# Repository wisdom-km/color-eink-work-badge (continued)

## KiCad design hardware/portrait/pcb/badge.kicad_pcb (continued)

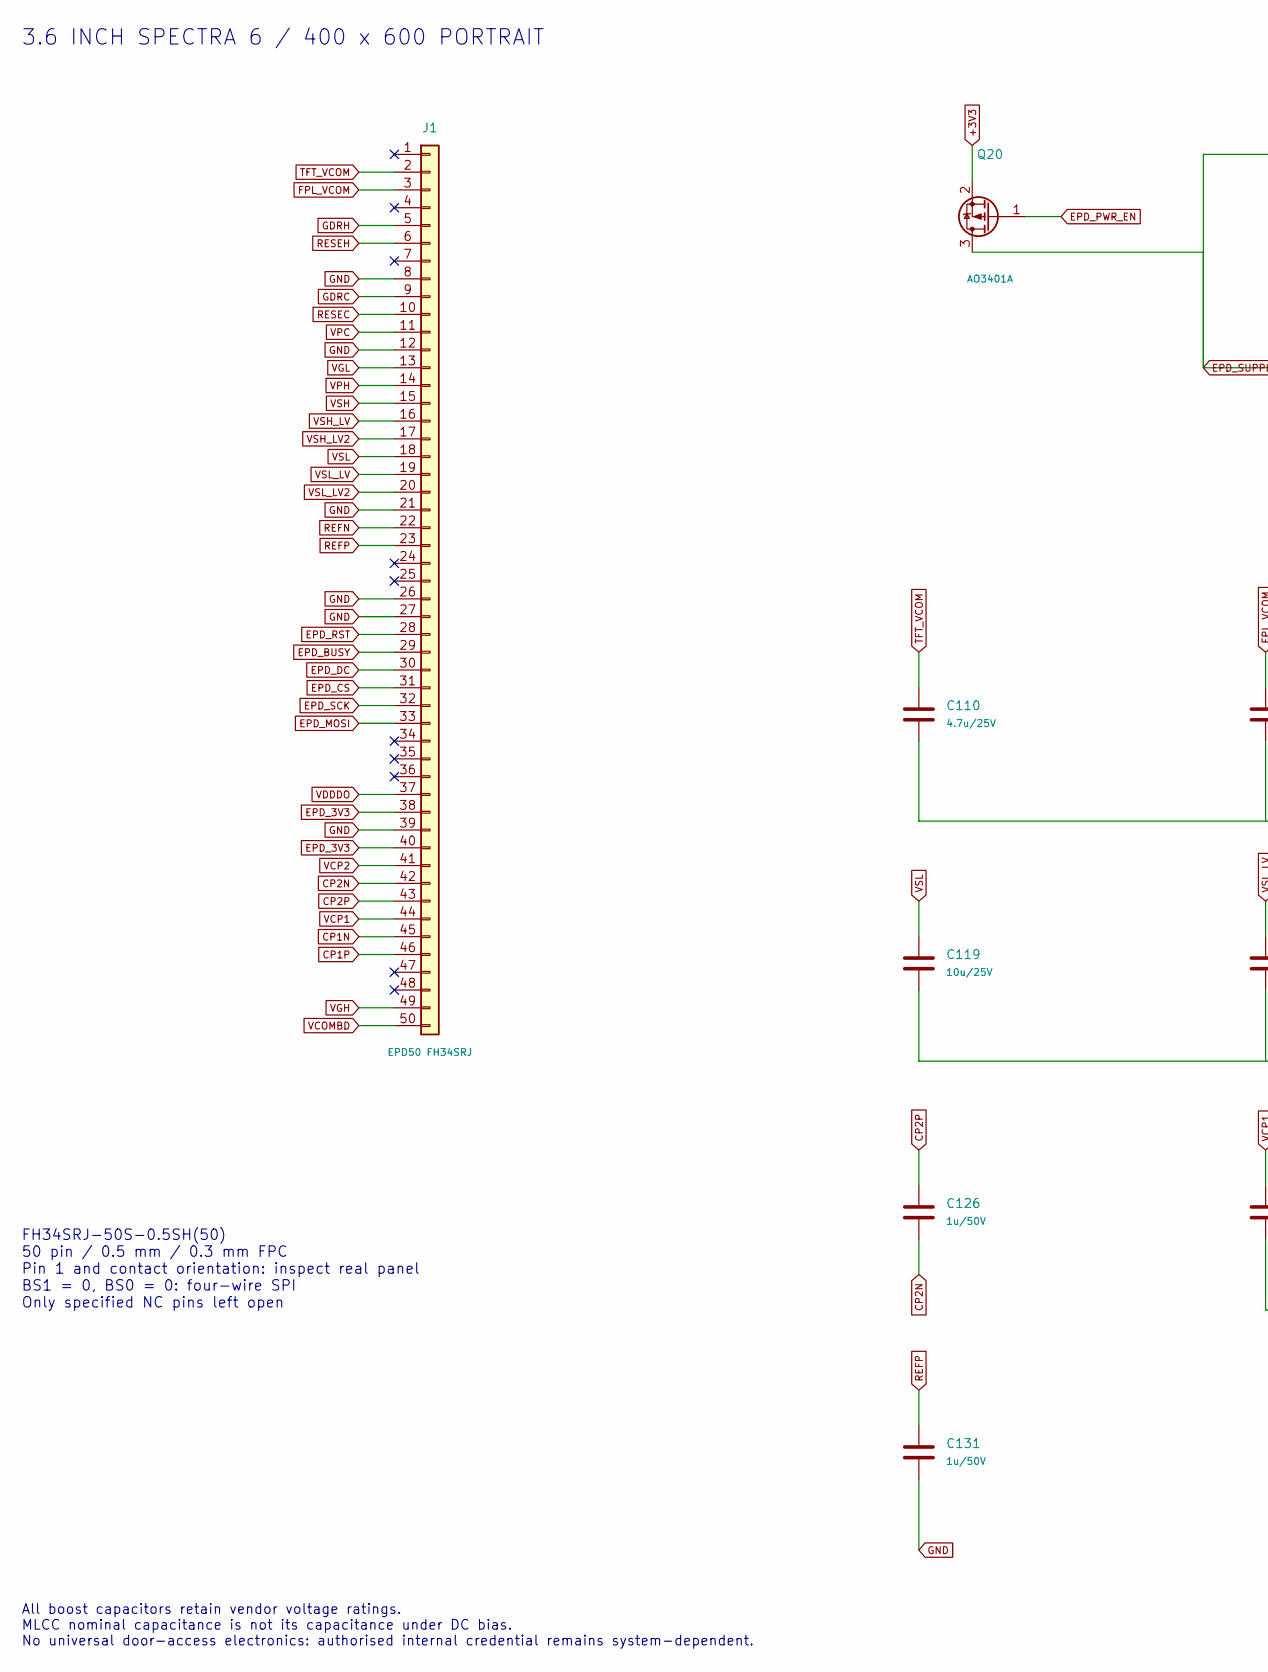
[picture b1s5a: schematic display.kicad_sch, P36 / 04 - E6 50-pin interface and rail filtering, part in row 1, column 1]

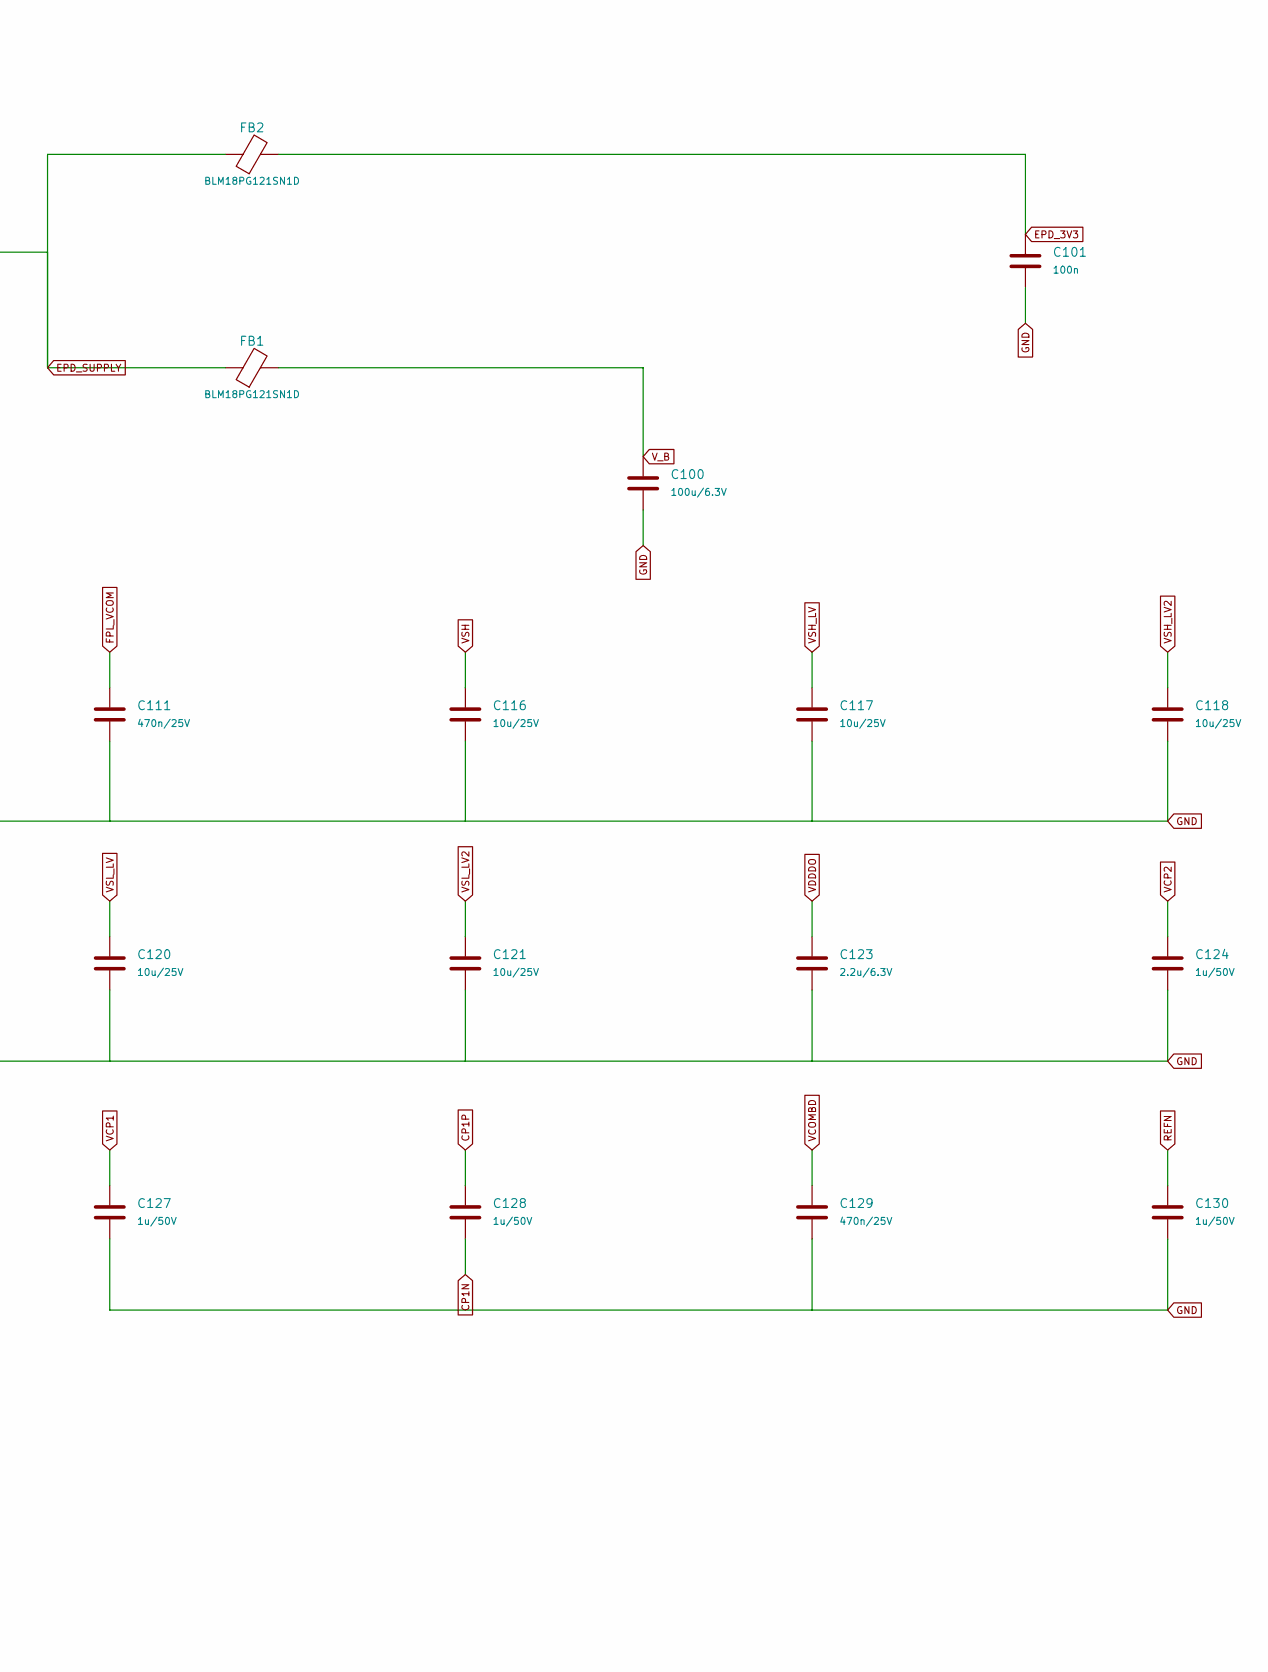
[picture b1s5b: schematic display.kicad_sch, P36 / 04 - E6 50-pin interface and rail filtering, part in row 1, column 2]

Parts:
C100: 100u/6.3V; C_1210_3225Metric
C101: 100n; C_0402_1005Metric
C110: 4.7u/25V; C_0805_2012Metric
C111, C129: 470n/25V; C_0805_2012Metric
C116, C117, C118, C119, C120, C121: 10u/25V; C_0805_2012Metric
C123: 2.2u/6.3V; C_0805_2012Metric
C124, C126, C127, C128, C130, C131: 1u/50V; C_0805_2012Metric
FB1, FB2: BLM18PG121SN1D; L_0603_1608Metric
J1: EPD50 FH34SRJ; FH34SRJ-50S-0.5SH
Q20: AO3401A; SOT-23

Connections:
+3V3: Q20.2 (S); also elsewhere on the board
CP1N: C128.2, J1.45
CP1P: C128.1, J1.46
CP2N: C126.2, J1.42
CP2P: C126.1, J1.43
EPD_3V3: C101.1, FB2.2, J1.38, J1.40
EPD_BUSY: J1.29; also elsewhere on the board
EPD_CS: J1.31; also elsewhere on the board
EPD_DC: J1.30; also elsewhere on the board
EPD_MOSI: J1.33; also elsewhere on the board
EPD_PWR_EN: Q20.1 (G); also elsewhere on the board
EPD_RST: J1.28; also elsewhere on the board
EPD_SCK: J1.32; also elsewhere on the board
EPD_SUPPLY: FB1.1, FB2.1, Q20.3 (D)
FPL_VCOM: C111.1, J1.3
GDRC: J1.9; also elsewhere on the board
GDRH: J1.5; also elsewhere on the board
GND: C100.2, C101.2, C110.2, C111.2, C116.2, C117.2, C118.2, C119.2, C120.2, C121.2, C123.2, C124.2, C127.2, C129.2, C130.2, C131.2, J1.8, J1.12, J1.21, J1.26, J1.27, J1.39; also elsewhere on the board
REFN: C130.1, J1.22
REFP: C131.1, J1.23
RESEC: J1.10; also elsewhere on the board
RESEH: J1.6; also elsewhere on the board
TFT_VCOM: C110.1, J1.2
VCOMBD: C129.1, J1.50
VCP1: C127.1, J1.44
VCP2: C124.1, J1.41
VDDDO: C123.1, J1.37
VGH: J1.49; also elsewhere on the board
VGL: J1.13; also elsewhere on the board
VPC: J1.11; also elsewhere on the board
VPH: J1.14; also elsewhere on the board
VSH: C116.1, J1.15
VSH_LV: C117.1, J1.16
VSH_LV2: C118.1, J1.17
VSL: C119.1, J1.18
VSL_LV: C120.1, J1.19
VSL_LV2: C121.1, J1.20
V_B: C100.1, FB1.2; also elsewhere on the board

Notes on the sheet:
3.6 INCH SPECTRA 6 / 400 x 600 PORTRAIT
FH34SRJ-50S-0.5SH(50) 50 pin / 0.5 mm / 0.3 mm FPC Pin 1 and contact orientation: inspect real panel BS1 = 0, BS0 = 0: four-wire SPI Only specified NC pins left open
All boost capacitors retain vendor voltage ratings. MLCC nominal capacitance is not its capacitance under DC bias. No universal door-access electronics: authorised internal credential remains system-dependent.

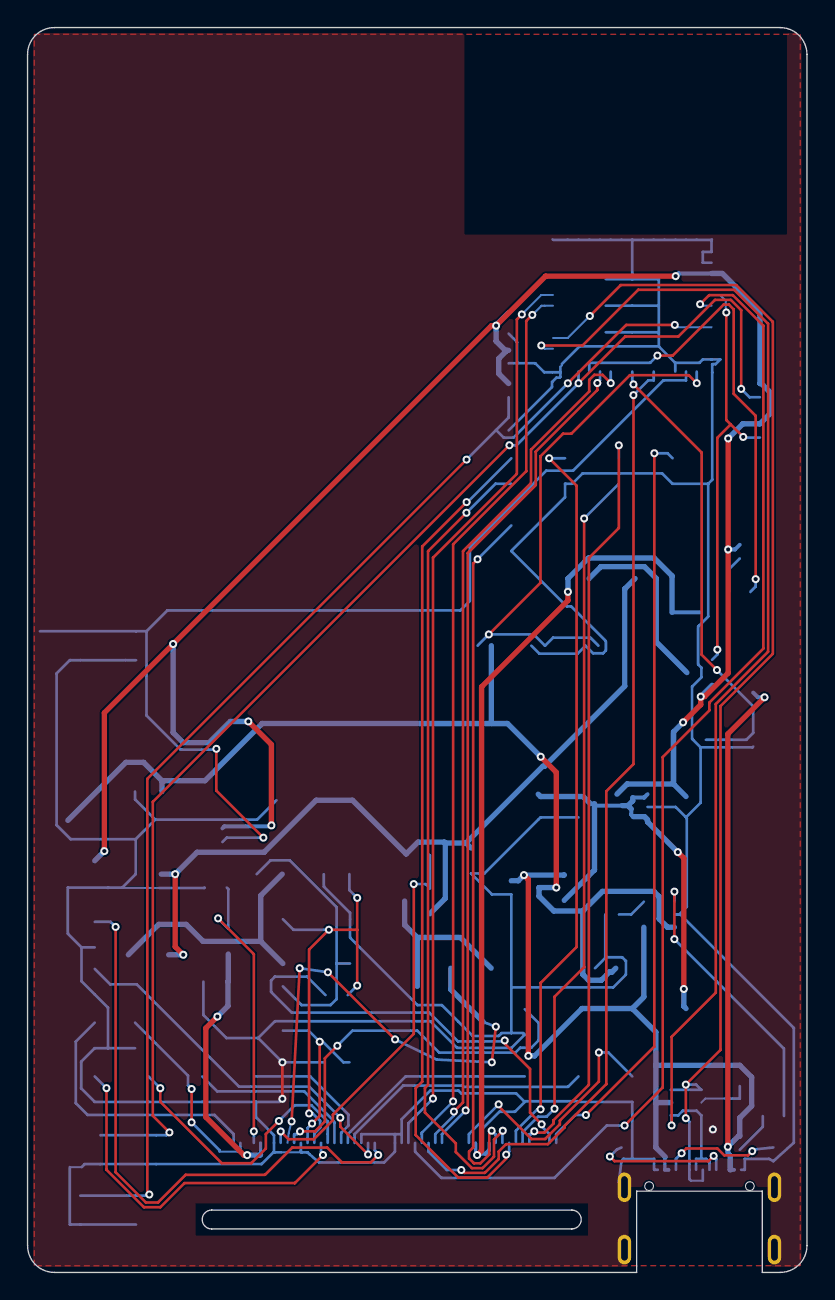
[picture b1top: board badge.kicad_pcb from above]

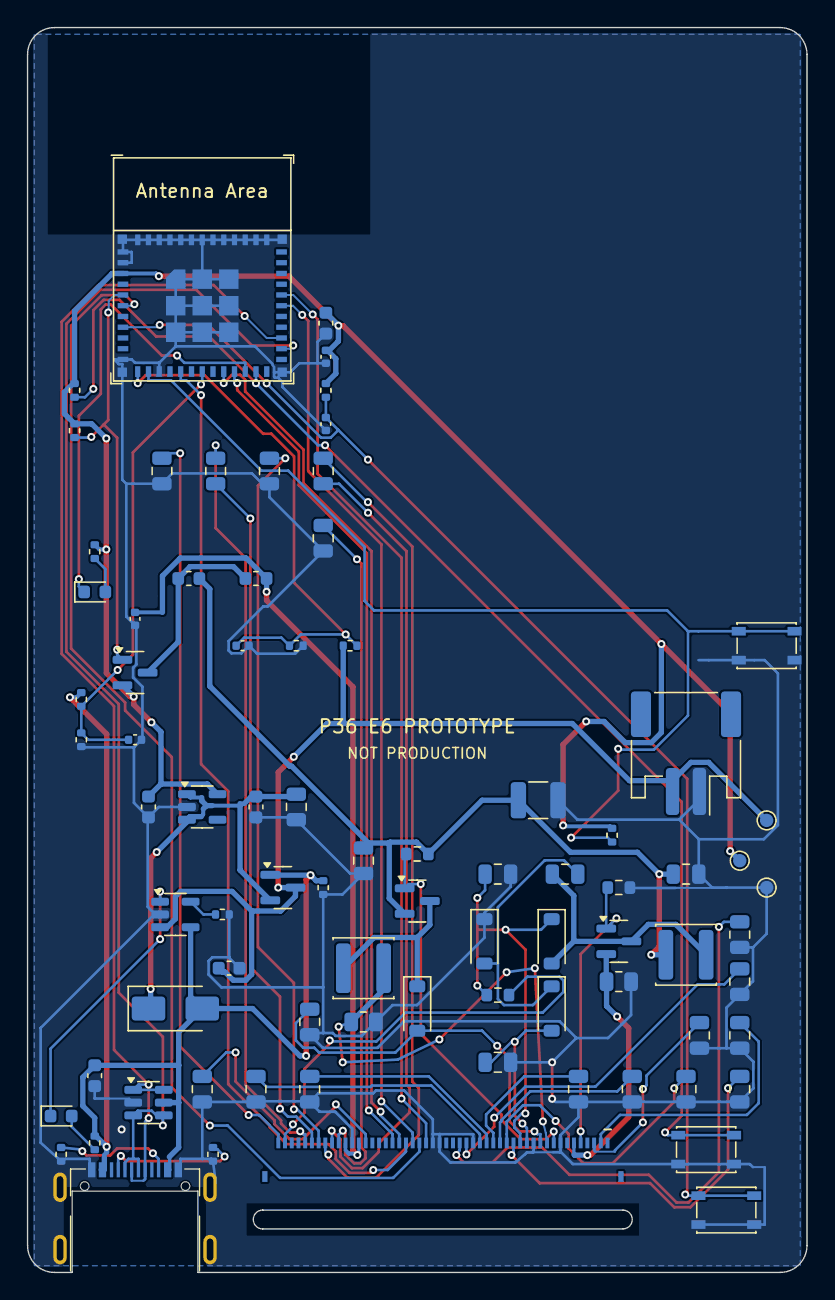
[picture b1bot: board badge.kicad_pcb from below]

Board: 2 copper layers, 58.0 x 92.6 mm, 81 parts (81 on the bottom side), 58 nets.

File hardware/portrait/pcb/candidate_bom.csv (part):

Reference,Value,Footprint,Description,DNP
J3,USB-C 16P 沉板 (TYPE-C-31-M-14),badge:TYPE-C-31-M-14,"HRO TYPE-C-31-M-14, 16P USB 2.0 mid-mount receptacle",False
R1,5.1k,Resistor_SMD:R_0402_1005Metric,5.1k 0402 1%,False
R2,5.1k,Resistor_SMD:R_0402_1005Metric,5.1k 0402 1%,False
C1,4.7u,Capacitor_SMD:C_0603_1608Metric,4.7uF 10V X5R 0603,False
U3,MCP73831T-2ACI/OT,Package_TO_SOT_SMD:SOT-23-5,Microchip MCP73831 4.2V charger; 10k PROG nominal100mA; protected single-cell LiPo only,False
R3,10k,Resistor_SMD:R_0402_1005Metric,"MCP73831 RPROG10k -> nominal100mA, verify actual cell rating",False
R4,1k,Resistor_SMD:R_0402_1005Metric,1k 0402 1%,False
D4,RED,LED_SMD:LED_0603_1608Metric,"LED 0603 red, charging indicator",False
C2,4.7u,Capacitor_SMD:C_0603_1608Metric,4.7uF 10V X5R 0603,False
J2,JST PH2.0 battery,Connector_JST:JST_PH_S2B-PH-SM4-TB_1x02-1MP_P2.00mm_Horizontal,JST S2B-PH-SM4-TB; Adafruit1578 keyedPHR2 mate: contact1GND/contact2VBAT; verify incoming lot keyedface+voltage beforepower; retain original lead,False
U4,XC6220B331MR-G,Package_TO_SOT_SMD:SOT-23-5,LDO 3.3V Iq 8uA 1A SOT-25 VIN/GND/CE/NC/VOUT. Torex 3.0-3.5V pair: CIN=10uF CL=4.7uF near U4.,False
C3,10u,Capacitor_SMD:C_0603_1608Metric,"10uF 6.3V X5R 0603 LDO CIN (Torex table, 3.3V with CL=4.7uF)",False
C4,4.7u,Capacitor_SMD:C_0603_1608Metric,4.7uF 10V X5R 0603 LDO CL near VOUT (Torex 3.00-3.50V + CIN=10uF),False
R5,1M,Resistor_SMD:R_0402_1005Metric,1M 0402 1%,False
R6,1M,Resistor_SMD:R_0402_1005Metric,1M 0402 1%,False
C5,100n,Capacitor_SMD:C_0402_1005Metric,100n 0402,False
TP4,VBAT,TestPoint:TestPoint_Pad_D1.0mm,test pad,False
TP2,3V3,TestPoint:TestPoint_Pad_D1.0mm,test pad,False
TP3,GND,TestPoint:TestPoint_Pad_D1.0mm,test pad,False
U1,ESP32-C3-MINI-1-N4X,badge:ESP32-C3-MINI-1,Espressif current C3 MINI1 N4X; module antenna clearance and RF on-body test required,False
C6,10u,Capacitor_SMD:C_0603_1608Metric,10uF 6.3V X5R 0603,False
C7,100n,Capacitor_SMD:C_0402_1005Metric,100n 0402,False
R7,10k,Resistor_SMD:R_0402_1005Metric,10k 0402 1%,False
C8,1u,Capacitor_SMD:C_0402_1005Metric,1u 0402,False
R8,10k,Resistor_SMD:R_0402_1005Metric,10k 0402 1%,False
R10,10k,Resistor_SMD:R_0402_1005Metric,10k 0402 1%,False
R9,1k,Resistor_SMD:R_0402_1005Metric,1k 0402 1%,False
D5,GREEN,LED_SMD:LED_0603_1608Metric,"LED 0603 green, status",False
SW1,RESET,Button_Switch_SMD:SW_SPST_PTS810,C&K PTS810; nominalheight2.5mm(+.2/-.1); travel.15+/-.1mm; actuator/flexure must be tested,False
SW2,BOOT/USER,Button_Switch_SMD:SW_SPST_PTS810,C&K PTS810; nominalheight2.5mm(+.2/-.1); travel.15+/-.1mm; actuator/flexure must be tested,False
Q10,AO3401A,Package_TO_SOT_SMD:SOT-23,"P-MOS battery load-share, sourceVSYS/drainVBAT; body diode VBAT->VSYS; AN1149 topology",False
R20,100k,Resistor_SMD:R_0402_1005Metric,100k 0402 1%,False
D10,SS14,Diode_SMD:D_SMA,USB to VSYS Schottky40V1A; evaluate thermal and droop,False
C30,22u,Capacitor_SMD:C_0805_2012Metric,22uF10V X5R0805,False
J1,EPD50 FH34SRJ,badge:FH34SRJ-50S-0.5SH,Hirose FH34SRJ-50S-0.5SH(50); .5pitch50P dualcontact .3FPC; pending footprint drawing verification,False
Q20,AO3401A,Package_TO_SOT_SMD:SOT-23,3V3 panel hard powergate; default10k gatepullup OFF; SPI pins hi-Z before poweroff,False
C100,100u/6.3V,Capacitor_SMD:C_1210_3225Metric,100uF6.3V X5R1210; effectivecap/inrush verify,False
C101,100n,Capacitor_SMD:C_0402_1005Metric,100n 0402,False
FB1,BLM18PG121SN1D,Inductor_SMD:L_0603_1608Metric,Murata BLM18PG121SN1D from vendorboost reference,False
L1,10uH,Inductor_SMD:L_Changjiang_FNR4018S,10uH shielded4x4x1.8; Isat>=1A target pending vendor peak-current test; no47uH substitute,False
L2,10uH,Inductor_SMD:L_Changjiang_FNR4018S,10uH shielded4x4x1.8; Isat>=1A target pending vendor peak-current test; no47uH substitute,False
Q1,AO3400A,Package_TO_SOT_SMD:SOT-23,N-MOS as vendorAO3400 stage,False
Q2,SI2301CDS-T1-E3,Package_TO_SOT_SMD:SOT-23,Vishay P-MOS exactly vendor negative-boost stage,False
R100,1M,Resistor_SMD:R_0603_1608Metric,1M; vendorstage; sense resistors0.2ohm>=0.25W,False
R101,0.2R,Resistor_SMD:R_0805_2012Metric,0.2R; vendorstage; sense resistors0.2ohm>=0.25W,False
R102,1M,Resistor_SMD:R_0603_1608Metric,1M; vendorstage; sense resistors0.2ohm>=0.25W,False
R103,0.2R,Resistor_SMD:R_0805_2012Metric,0.2R; vendorstage; sense resistors0.2ohm>=0.25W,False
R104,0R,Resistor_SMD:R_0603_1608Metric,0R; vendorstage; sense resistors0.2ohm>=0.25W,False
D1,MBR0530,Diode_SMD:D_SOD-123,30V0.5A Schottky as vendor reference; pin1K pin2A,False
D2,MBR0530,Diode_SMD:D_SOD-123,30V0.5A Schottky as vendor reference; pin1K pin2A,False
D3,MBR0530,Diode_SMD:D_SOD-123,30V0.5A Schottky as vendor reference; pin1K pin2A,False
D6,MBR0530,Diode_SMD:D_SOD-123,30V0.5A Schottky as vendor reference; pin1K pin2A,False
C110,4.7u/25V,Capacitor_SMD:C_0805_2012Metric,4.7u/25V X7R/X5R0805; voltage-rated; DC-bias capacitance vendor verification required,False
C111,470n/25V,Capacitor_SMD:C_0805_2012Metric,470n/25V X7R/X5R0805; voltage-rated; DC-bias capacitance vendor verification required,False
C112,10u/25V,Capacitor_SMD:C_0805_2012Metric,10u/25V X7R/X5R0805; voltage-rated; DC-bias capacitance vendor verification required,False
C113,10u/25V,Capacitor_SMD:C_0805_2012Metric,10u/25V X7R/X5R0805; voltage-rated; DC-bias capacitance vendor verification required,False
C114,4.7u/25V,Capacitor_SMD:C_0805_2012Metric,4.7u/25V X7R/X5R0805; voltage-rated; DC-bias capacitance vendor verification required,False
C115,10u/25V,Capacitor_SMD:C_0805_2012Metric,10u/25V X7R/X5R0805; voltage-rated; DC-bias capacitance vendor verification required,False
C116,10u/25V,Capacitor_SMD:C_0805_2012Metric,10u/25V X7R/X5R0805; voltage-rated; DC-bias capacitance vendor verification required,False
C117,10u/25V,Capacitor_SMD:C_0805_2012Metric,10u/25V X7R/X5R0805; voltage-rated; DC-bias capacitance vendor verification required,False
C118,10u/25V,Capacitor_SMD:C_0805_2012Metric,10u/25V X7R/X5R0805; voltage-rated; DC-bias capacitance vendor verification required,False
C119,10u/25V,Capacitor_SMD:C_0805_2012Metric,10u/25V X7R/X5R0805; voltage-rated; DC-bias capacitance vendor verification required,False
C120,10u/25V,Capacitor_SMD:C_0805_2012Metric,10u/25V X7R/X5R0805; voltage-rated; DC-bias capacitance vendor verification required,False
C121,10u/25V,Capacitor_SMD:C_0805_2012Metric,10u/25V X7R/X5R0805; voltage-rated; DC-bias capacitance vendor verification required,False
C122,4.7u/25V,Capacitor_SMD:C_0805_2012Metric,4.7u/25V X7R/X5R0805; voltage-rated; DC-bias capacitance vendor verification required,False
C123,2.2u/6.3V,Capacitor_SMD:C_0805_2012Metric,2.2u/6.3V X7R/X5R0805; voltage-rated; DC-bias capacitance vendor verification required,False
C124,1u/50V,Capacitor_SMD:C_0805_2012Metric,1u/50V X7R/X5R0805; voltage-rated; DC-bias capacitance vendor verification required,False
C125,10u/25V,Capacitor_SMD:C_0805_2012Metric,10u/25V X7R/X5R0805; voltage-rated; DC-bias capacitance vendor verification required,False
C126,1u/50V,Capacitor_SMD:C_0805_2012Metric,1u/50V X7R/X5R0805; voltage-rated; DC-bias capacitance vendor verification required,False
C127,1u/50V,Capacitor_SMD:C_0805_2012Metric,1u/50V X7R/X5R0805; voltage-rated; DC-bias capacitance vendor verification required,False
C128,1u/50V,Capacitor_SMD:C_0805_2012Metric,1u/50V X7R/X5R0805; voltage-rated; DC-bias capacitance vendor verification required,False
C129,470n/25V,Capacitor_SMD:C_0805_2012Metric,470n/25V X7R/X5R0805; voltage-rated; DC-bias capacitance vendor verification required,False
C130,1u/50V,Capacitor_SMD:C_0805_2012Metric,1u/50V X7R/X5R0805; voltage-rated; DC-bias capacitance vendor verification required,False
C131,1u/50V,Capacitor_SMD:C_0805_2012Metric,1u/50V X7R/X5R0805; voltage-rated; DC-bias capacitance vendor verification required,False
U5,USBLC6-2SC6,Package_TO_SOT_SMD:SOT-23-6,ST USBLC6-2SC6; DS4260pinmap; short GNDreturn; systemESDtest pending,False
FB2,BLM18PG121SN1D,Inductor_SMD:L_0603_1608Metric,Separate logic ferrite branch as vendor reference; EPD_SUPPLY is gated3V3,False
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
